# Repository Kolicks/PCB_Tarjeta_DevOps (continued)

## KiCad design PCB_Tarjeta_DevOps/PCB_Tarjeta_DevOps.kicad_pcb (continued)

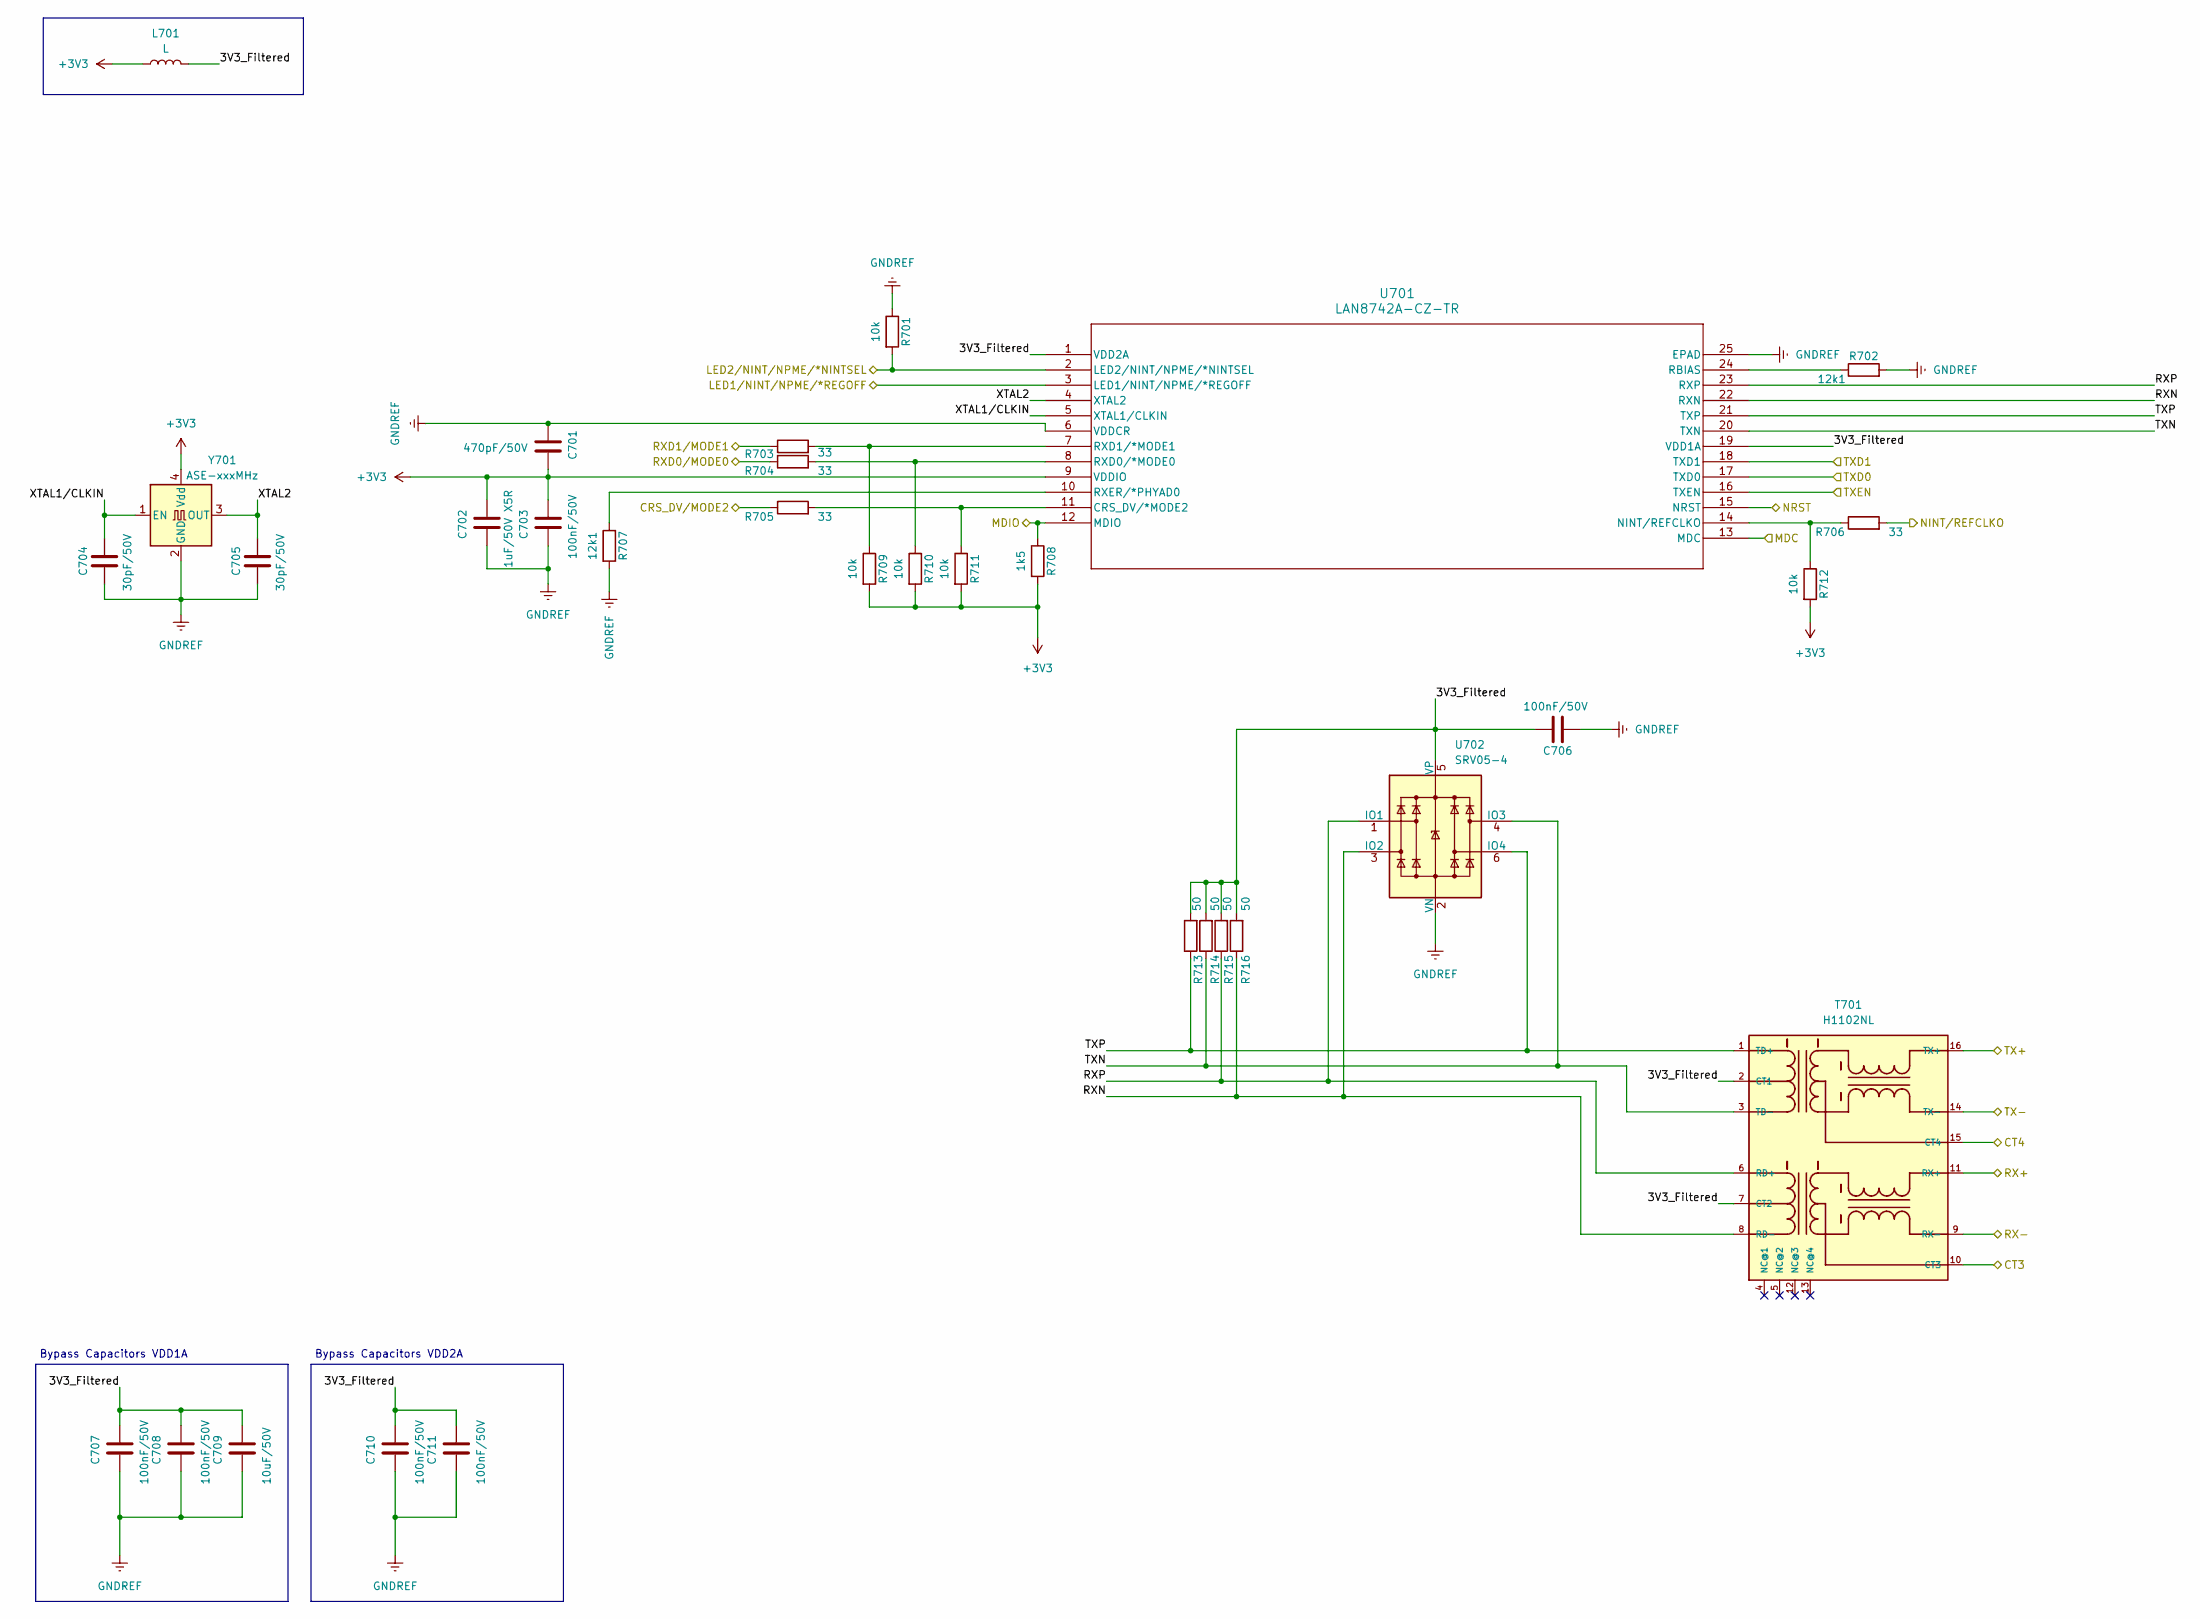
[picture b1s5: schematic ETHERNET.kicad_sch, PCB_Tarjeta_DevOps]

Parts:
C701: 470pF/50V; C_0603_1608Metric_Pad1.08x0.95mm_HandSolder
C702: 1uF/50V X5R; C_0603_1608Metric_Pad1.08x0.95mm_HandSolder
C703, C706, C707, C708, C710, C711: 100nF/50V; C_0603_1608Metric_Pad1.08x0.95mm_HandSolder
C704, C705: 30pF/50V; C_0603_1608Metric_Pad1.08x0.95mm_HandSolder
C709: 10uF/50V; C_0603_1608Metric_Pad1.08x0.95mm_HandSolder
L701: L; L_0603_1608Metric_Pad1.05x0.95mm_HandSolder
R701, R709, R710, R711, R712: 10k; R_0603_1608Metric_Pad0.98x0.95mm_HandSolder
R702, R707: 12k1; R_0603_1608Metric_Pad0.98x0.95mm_HandSolder
R703, R704, R705, R706: 33; R_0603_1608Metric_Pad0.98x0.95mm_HandSolder
R708: 1k5; R_0603_1608Metric_Pad0.98x0.95mm_HandSolder
R713, R714, R715, R716: 50; R_0603_1608Metric_Pad0.98x0.95mm_HandSolder
T701: H1102NL
U701: LAN8742A-CZ-TR; SQFN24_4X4MC_MCH
U702: SRV05-4; SOT-23-6
Y701: ASE-xxxMHz; Oscillator_SMD_EuroQuartz_XO53-4Pin_5.0x3.2mm_HandSoldering

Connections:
+3V3: C701.1, C702.1, C703.1, L701.1, R708.2, R709.2, R710.2, R711.2, R712.2, U701.9 (VDDIO), Y701.4 (Vdd); also elsewhere on the board
/DEBUGGER/NRST: U701.15 (NRST); also elsewhere on the board
/ETHERNET/3V3_Filtered: C706.1, C707.1, C708.1, C709.1, C710.1, C711.1, L701.2, R713.2, R714.2, R715.2, R716.2, T701.2 (CT1), T701.7 (CT2), U701.1 (VDD2A), U701.19 (VDD1A), U702.5 (VP)
/ETHERNET/CRS_DV/MODE2: R705.1; also elsewhere on the board
/ETHERNET/CT3: T701.10 (CT3); also elsewhere on the board
/ETHERNET/CT4: T701.15 (CT4); also elsewhere on the board
/ETHERNET/LED1/NINT/NPME/*REGOFF: U701.3 (LED1/NINT/NPME/*REGOFF); also elsewhere on the board
/ETHERNET/LED2/NINT/NPME/*NINTSEL: R701.2, U701.2 (LED2/NINT/NPME/*NINTSEL); also elsewhere on the board
/ETHERNET/MDC: U701.13 (MDC); also elsewhere on the board
/ETHERNET/MDIO: R708.1, U701.12 (MDIO); also elsewhere on the board
/ETHERNET/NINT/REFCLKO: R706.2; also elsewhere on the board
/ETHERNET/RX+: T701.11 (RX+); also elsewhere on the board
/ETHERNET/RX-: T701.9 (RX-); also elsewhere on the board
/ETHERNET/RXD0/MODE0: R704.1; also elsewhere on the board
/ETHERNET/RXD1/MODE1: R703.1; also elsewhere on the board
/ETHERNET/RXN: R716.1, T701.8 (RD-), U701.22 (RXN), U702.3 (IO2)
/ETHERNET/RXP: R715.1, T701.6 (RD+), U701.23 (RXP), U702.1 (IO1)
/ETHERNET/TX+: T701.16 (TX+); also elsewhere on the board
/ETHERNET/TX-: T701.14 (TX-); also elsewhere on the board
/ETHERNET/TXD0: U701.17 (TXD0); also elsewhere on the board
/ETHERNET/TXD1: U701.18 (TXD1); also elsewhere on the board
/ETHERNET/TXEN: U701.16 (TXEN); also elsewhere on the board
/ETHERNET/TXN: R714.1, T701.3 (TD-), U701.20 (TXN), U702.4 (IO3)
/ETHERNET/TXP: R713.1, T701.1 (TD+), U701.21 (TXP), U702.6 (IO4)
/ETHERNET/XTAL1/CLKIN: C704.1, U701.5 (XTAL1/CLKIN), Y701.1 (EN)
/ETHERNET/XTAL2: C705.1, U701.4 (XTAL2), Y701.3 (OUT)
GNDREF: C701.2, C702.2, C703.2, C704.2, C705.2, C706.2, C707.2, C708.2, C709.2, C710.2, C711.2, R701.1, R702.2, R707.2, U701.6 (VDDCR), U701.25 (EPAD), U702.2 (VN), Y701.2 (GND); also elsewhere on the board
unnamed: R705.2, R711.1, U701.11 (CRS_DV/*MODE2)
unnamed: R706.1, R712.1, U701.14 (NINT/REFCLKO)
unnamed: R702.1, U701.24 (RBIAS)
unnamed: R704.2, R710.1, U701.8 (RXD0/*MODE0)
unnamed: R703.2, R709.1, U701.7 (RXD1/*MODE1)
unnamed: R707.1, U701.10 (RXER/*PHYAD0)

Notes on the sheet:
Bypass Capacitors VDD1A
Bypass Capacitors VDD2A

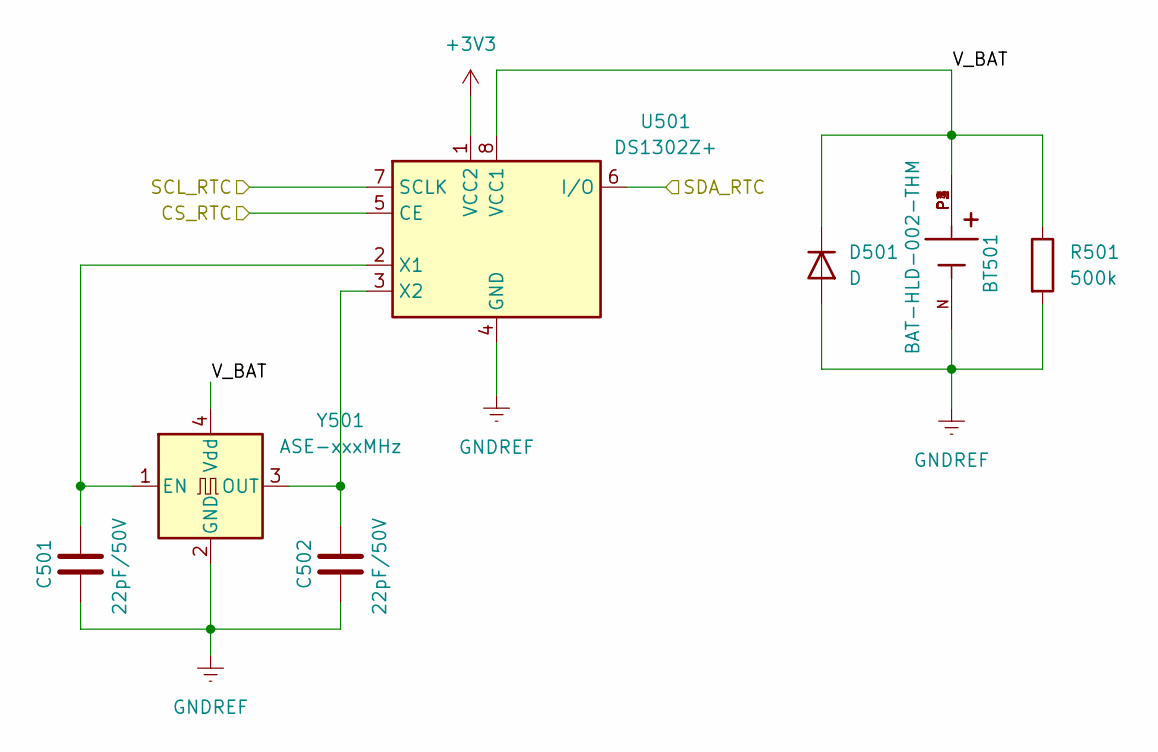
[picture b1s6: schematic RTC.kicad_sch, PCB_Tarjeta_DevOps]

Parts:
BT501: BAT-HLD-002-THM; BAT_BAT-HLD-002-THM; PARTREV C
C501, C502: 22pF/50V; C_0603_1608Metric_Pad1.08x0.95mm_HandSolder
D501: D; D_SMA_Handsoldering
R501: 500k; R_0603_1608Metric_Pad0.98x0.95mm_HandSolder
U501: DS1302Z+; DIP-8_W7.62mm_Socket_LongPads
Y501: ASE-xxxMHz; Oscillator_SMD_EuroQuartz_XO53-4Pin_5.0x3.2mm_HandSoldering

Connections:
+3V3: U501.1 (VCC2); also elsewhere on the board
/MCU/CS_RTC: U501.5 (CE); also elsewhere on the board
/MCU/SCL_RTC: U501.7 (SCLK); also elsewhere on the board
/MCU/SDA_RTC: U501.6 (I/O); also elsewhere on the board
/RTC/V_BAT: BT501.P1, BT501.P2, BT501.P3, BT501.P4, D501.1 (K), R501.1, U501.8 (VCC1), Y501.4 (Vdd)
GNDREF: BT501.N, C501.2, C502.2, D501.2 (A), R501.2, U501.4 (GND), Y501.2 (GND); also elsewhere on the board
unnamed: C501.1, U501.2 (X1), Y501.1 (EN)
unnamed: C502.1, U501.3 (X2), Y501.3 (OUT)

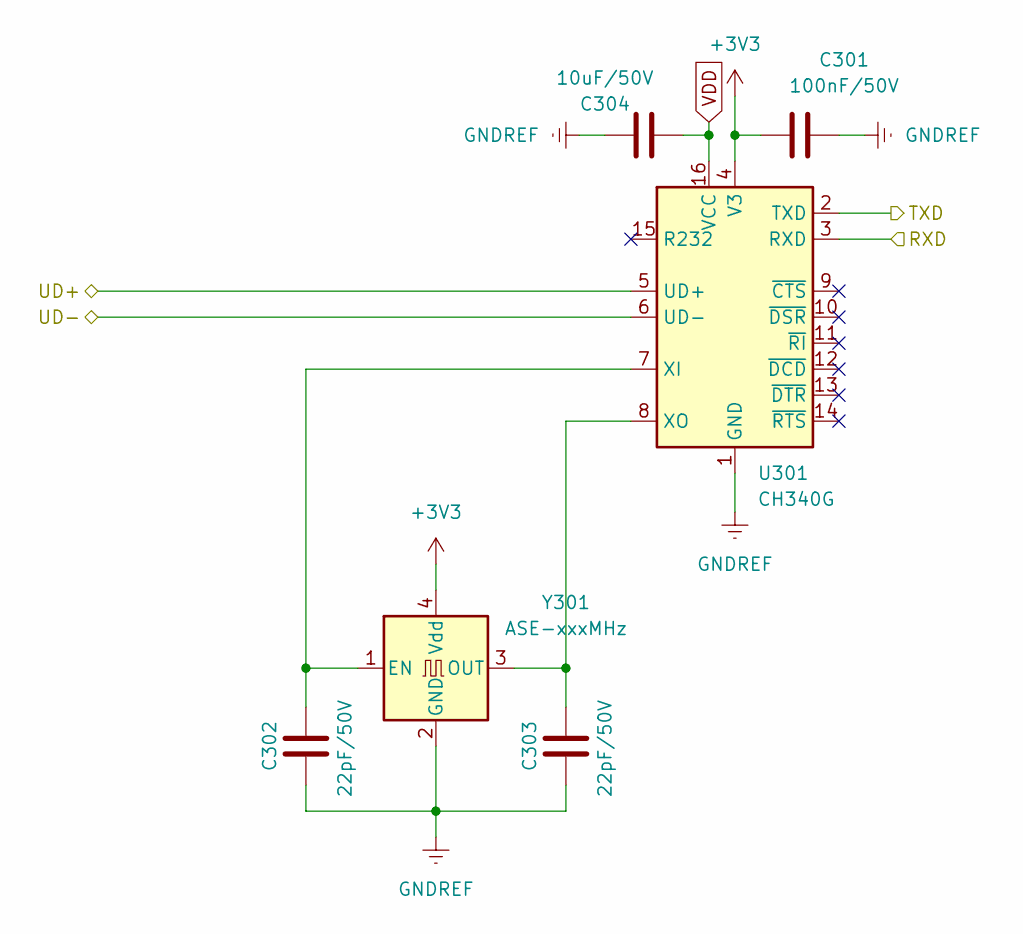
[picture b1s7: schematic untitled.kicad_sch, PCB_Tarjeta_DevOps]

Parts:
C301: 100nF/50V; C_0603_1608Metric_Pad1.08x0.95mm_HandSolder
C302, C303: 22pF/50V; C_0603_1608Metric_Pad1.08x0.95mm_HandSolder
C304: 10uF/50V; C_0603_1608Metric_Pad1.08x0.95mm_HandSolder
U301: CH340G; SOIC-16_3.9x9.9mm_P1.27mm
Y301: ASE-xxxMHz; Oscillator_SMD_EuroQuartz_XO53-4Pin_5.0x3.2mm_HandSoldering

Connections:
+3V3: C301.1, U301.4 (V3), Y301.4 (Vdd); also elsewhere on the board
/MCU/RX0: U301.3 (RXD); also elsewhere on the board
/MCU/TX0: U301.2 (TXD); also elsewhere on the board
/USB-UART/UD+: U301.5 (UD+); also elsewhere on the board
/USB-UART/UD-: U301.6 (UD-); also elsewhere on the board
GNDREF: C301.2, C302.2, C303.2, C304.2, U301.1 (GND), Y301.2 (GND); also elsewhere on the board
unnamed: C302.1, U301.7 (XI), Y301.1 (EN)
unnamed: C303.1, U301.8 (XO), Y301.3 (OUT)
VDD: C304.1, U301.16 (VCC); also elsewhere on the board

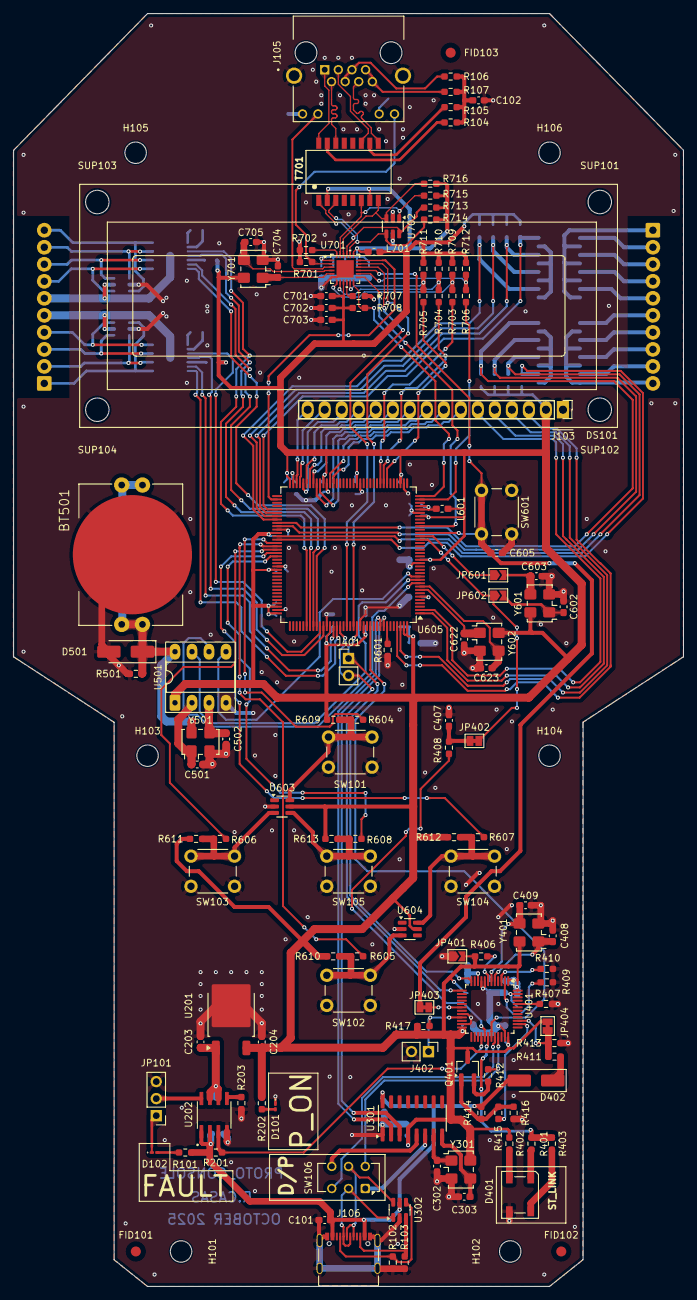
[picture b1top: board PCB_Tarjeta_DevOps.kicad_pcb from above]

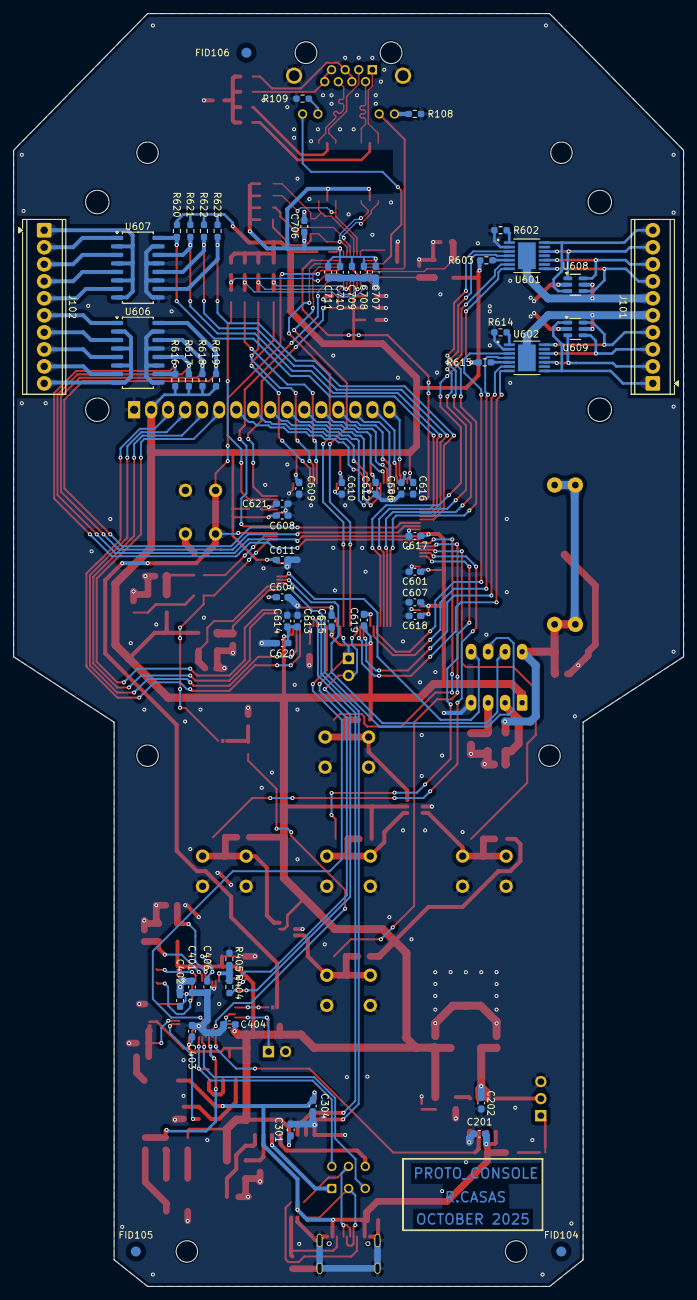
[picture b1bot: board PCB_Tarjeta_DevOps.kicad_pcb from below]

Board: 2 copper layers, 100.0 x 190.0 mm, 195 parts (60 on the bottom side), 161 nets.

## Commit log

2025-10-28 Fix link to CERN OHL website in README
    Updated the link for more information in the README.
2025-10-28 Update repository structure section in README
2025-10-28 Adjust image height for 3D PCB renders
    Updated image dimensions for 3D renders in README.
